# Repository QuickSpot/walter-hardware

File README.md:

# Walter hardware

## Introduction

In this repository you can find all information about Walter's hardware. The
hardware is designed using KiCad but we also support Altium designer footprints.
Besides footprints you can also find:
 - Datasheets
 - 3D renders
 - Schematics

Datasheets are published as PDF and are constructed using LaTeX. We welcome any
pull request on the datasheets to make sure all information that is required is
present.

## License

All files in this repository are published under the GPLv3 license.

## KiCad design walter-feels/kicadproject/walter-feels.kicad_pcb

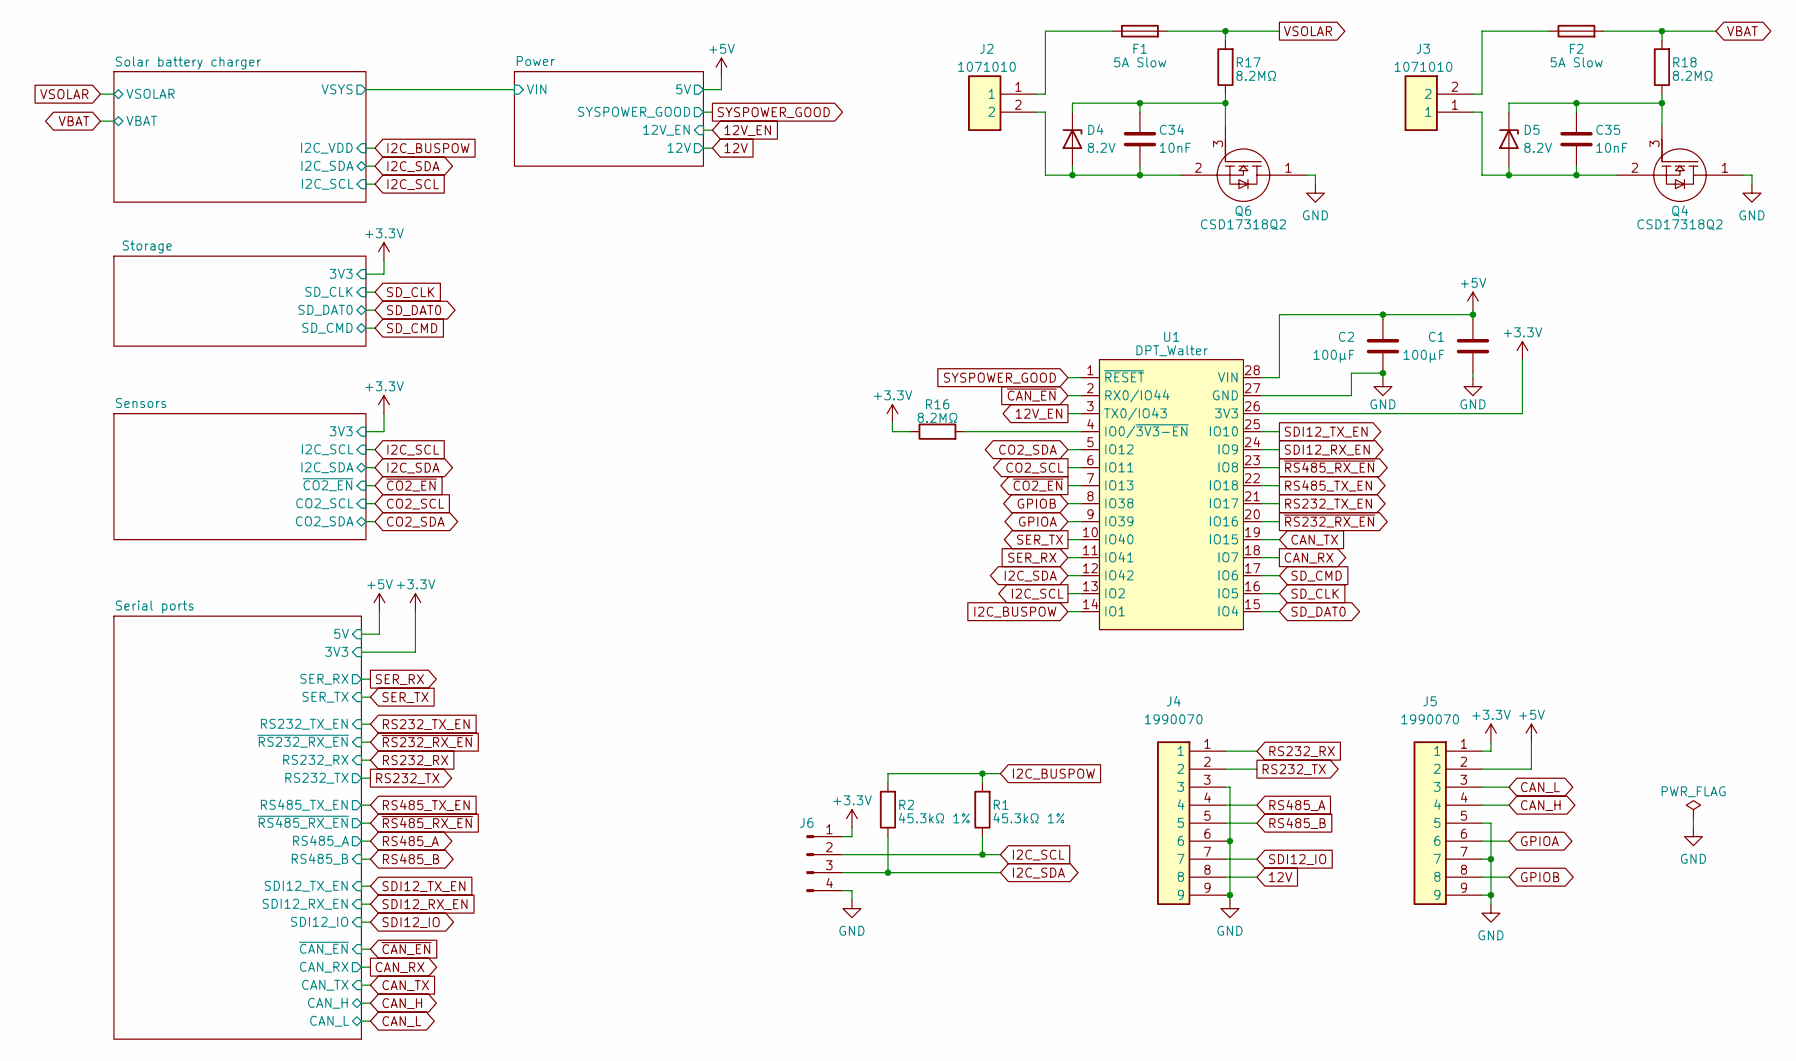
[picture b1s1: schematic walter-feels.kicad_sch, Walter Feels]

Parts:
C1, C2: 100µF; C_1210_3225Metric; JLCPCB C49066
C34, C35: 10nF; C_0603_1608Metric; JLCPCB C57112
D4, D5: 8.2V; D_SOD-523; PARTNO MM5Z8V2T1G; JLCPCB C99679
F1, F2: 5A Slow; Fuse_1206_3216Metric; JLCPCB C2691999
J2, J3: 1071010; JLCPCB C3310307
J4, J5: 1990070; JLCPCB C17275119
J6: Conn_01x04_Male; PinHeader_1x04_P2.54mm_Vertical; JLCPCB C5116483
Q4, Q6: CSD17318Q2
R1, R2: 45.3kΩ 1%; R_0603_1608Metric; JLCPCB C209146
R16, R17, R18: 8.2MΩ; R_0603_1608Metric; JLCPCB C13323
U1: DPT_Walter; walter-socket

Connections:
12V: J4.8; also elsewhere on the board
12V_EN: U1.3 (TX0/IO43); also elsewhere on the board
+3.3V: J5.1, J6.1, R16.1, U1.26 (3V3); also elsewhere on the board
+5V: C1.1, C2.1, J5.2, U1.28 (VIN); also elsewhere on the board
CAN_H: J5.4; also elsewhere on the board
CAN_L: J5.3; also elsewhere on the board
CAN_RX: U1.18 (IO7); also elsewhere on the board
CAN_TX: U1.19 (IO15); also elsewhere on the board
CO2_SCL: U1.6 (IO11); also elsewhere on the board
CO2_SDA: U1.5 (IO12); also elsewhere on the board
GND: C1.2, C2.2, J4.3, J4.6, J4.9, J5.5, J5.7, J5.9, J6.4, Q4.1, Q6.1, U1.27 (GND); also elsewhere on the board
GPIOA: J5.6, U1.9 (IO39)
GPIOB: J5.8, U1.8 (IO38)
I2C_BUSPOW: R1.2, R2.2, U1.14 (IO1); also elsewhere on the board
I2C_SCL: J6.2, R1.1, U1.13 (IO2); also elsewhere on the board
I2C_SDA: J6.3, R2.1, U1.12 (IO42); also elsewhere on the board
unnamed: C34.1, D4.1 (K), Q6.3, R17.1
unnamed: C34.2, D4.2 (A), J2.2, Q6.2
unnamed: C35.1, D5.1 (K), Q4.3, R18.1
unnamed: C35.2, D5.2 (A), J3.1, Q4.2
unnamed: F1.1, J2.1
unnamed: F2.1, J3.2
unnamed: R16.2, U1.4 (IO0/~3V3-EN)
RS232_RX: J4.1; also elsewhere on the board
RS232_TX: J4.2; also elsewhere on the board
RS232_TX_EN: U1.21 (IO17); also elsewhere on the board
RS485_A: J4.4; also elsewhere on the board
RS485_B: J4.5; also elsewhere on the board
RS485_TX_EN: U1.22 (IO18); also elsewhere on the board
SDI12_IO: J4.7; also elsewhere on the board
SDI12_RX_EN: U1.24 (IO9); also elsewhere on the board
SDI12_TX_EN: U1.25 (IO10); also elsewhere on the board
SD_CLK: U1.16 (IO5); also elsewhere on the board
SD_CMD: U1.17 (IO6); also elsewhere on the board
SD_DAT0: U1.15 (IO4); also elsewhere on the board
SER_RX: U1.11 (IO41); also elsewhere on the board
SER_TX: U1.10 (IO40); also elsewhere on the board
SYSPOWER_GOOD: U1.1 (~RESET); also elsewhere on the board
VBAT: F2.2, R18.2; also elsewhere on the board
VSOLAR: F1.2, R17.2; also elsewhere on the board
~CAN_EN: U1.2 (RX0/IO44); also elsewhere on the board
~CO2_EN: U1.7 (IO13); also elsewhere on the board
~RS232_RX_EN: U1.20 (IO16); also elsewhere on the board
~RS485_RX_EN: U1.23 (IO8); also elsewhere on the board

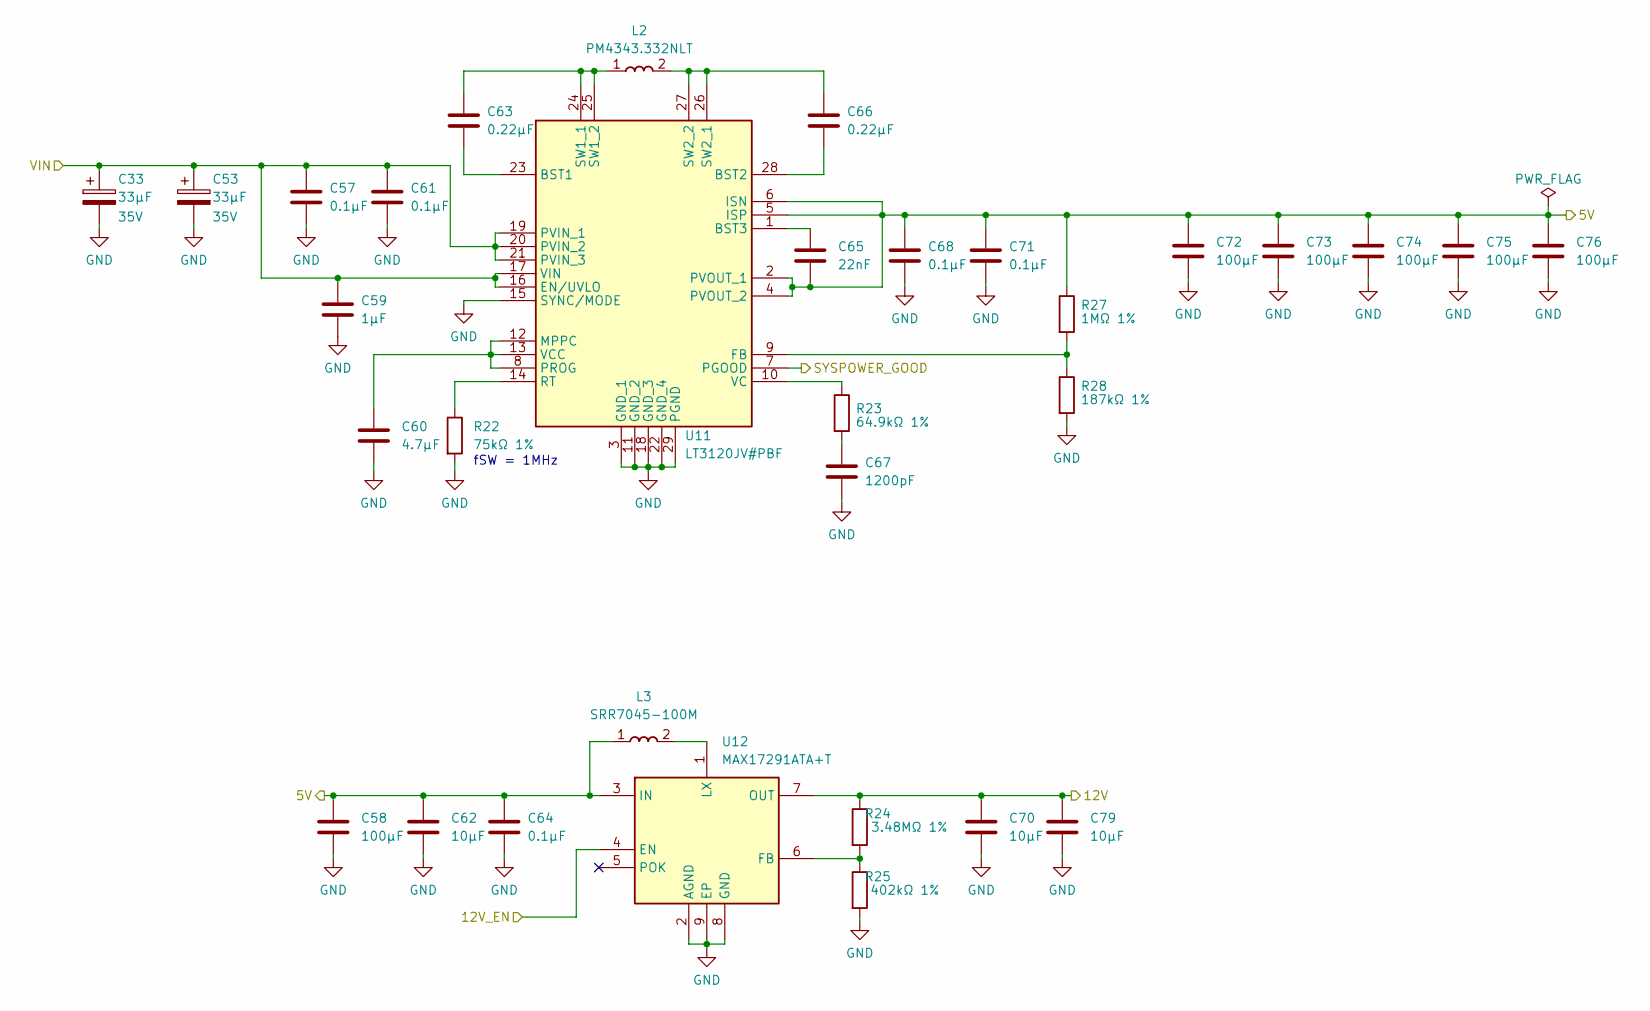
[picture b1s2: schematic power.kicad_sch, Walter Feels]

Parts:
C33, C53: 33µF; CP_EIA-7343-30_AVX-N; Voltage 35V; JLCPCB C2158306
C57, C61, C64, C68, C71: 0.1µF; C_0603_1608Metric; JLCPCB C14663
C58, C72, C73, C74, C75, C76: 100µF; C_1210_3225Metric; JLCPCB C49066
C59: 1μF; C_0603_1608Metric; JLCPCB C15849
C60: 4.7μF; C_0603_1608Metric; JLCPCB C19666
C62, C70, C79: 10µF; C_1206_3216Metric; JLCPCB C13585
C63, C66: 0.22µF; C_0603_1608Metric; JLCPCB C21120
C65: 22nF; C_0603_1608Metric; JLCPCB C21122
C67: 1200pF; C_0603_1608Metric; JLCPCB C30615
L2: PM4343.332NLT; INDPM140128X650N; JLCPCB C2594689
L3: SRR7045-100M; SRR7045100M; JLCPCB C1329516
R22: 75kΩ 1%; R_0603_1608Metric; JLCPCB C23242
R23: 64.9kΩ 1%; R_0603_1608Metric; JLCPCB C14891
R24: 3.48MΩ 1%; R_0603_1608Metric; JLCPCB C422936
R25: 402kΩ 1%; R_0603_1608Metric; JLCPCB C2960796
R27: 1MΩ 1%; R_0603_1608Metric; JLCPCB C22935
R28: 187kΩ 1%; R_0603_1608Metric; JLCPCB C321764
U11: LT3120JV#PBF; QFN50P400X500X83-29N-D; JLCPCB C3198178
U12: MAX17291ATA+T; SON50P200X200X80-9N-D; JLCPCB C7456683

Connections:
12V: C70.1, C79.1, R24.1, U12.7 (OUT); also elsewhere on the board
12V_EN: U12.4 (EN); also elsewhere on the board
+5V: C58.1, C62.1, C64.1, C65.2, C68.1, C71.1, C72.1, C73.1, C74.1, C75.1, C76.1, L3.1, R27.1, U11.2 (PVOUT_1), U11.4 (PVOUT_2), U11.5 (ISP), U11.6 (ISN), U12.3 (IN); also elsewhere on the board
/Power/VIN: C33.1, C53.1, C57.1, C59.2, C61.1, U11.16 (EN/UVLO), U11.17 (VIN), U11.19 (PVIN_1), U11.20 (PVIN_2), U11.21 (PVIN_3); also elsewhere on the board
GND: C33.2, C53.2, C57.2, C58.2, C59.1, C60.1, C61.2, C62.2, C64.2, C67.2, C68.2, C70.2, C71.2, C72.2, C73.2, C74.2, C75.2, C76.2, C79.2, R22.2, R25.2, R28.2, U11.3 (GND_1), U11.11 (GND_2), U11.15 (SYNC/MODE), U11.18 (GND_3), U11.22 (GND_4), U11.29 (PGND), U12.2 (AGND), U12.8 (GND), U12.9 (EP); also elsewhere on the board
unnamed: C60.2, U11.8 (PROG), U11.12 (MPPC), U11.13 (VCC)
unnamed: C63.1, L2.1, U11.24 (SW1_1), U11.25 (SW1_2)
unnamed: C63.2, U11.23 (BST1)
unnamed: C65.1, U11.1 (BST3)
unnamed: C66.1, L2.2, U11.26 (SW2_1), U11.27 (SW2_2)
unnamed: C66.2, U11.28 (BST2)
unnamed: C67.1, R23.2
unnamed: L3.2, U12.1 (LX)
unnamed: R22.1, U11.14 (RT)
unnamed: R23.1, U11.10 (VC)
unnamed: R24.2, R25.1, U12.6 (FB)
unnamed: R27.2, R28.1, U11.9 (FB)
SYSPOWER_GOOD: U11.7 (PGOOD); also elsewhere on the board

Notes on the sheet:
fSW = 1MHz

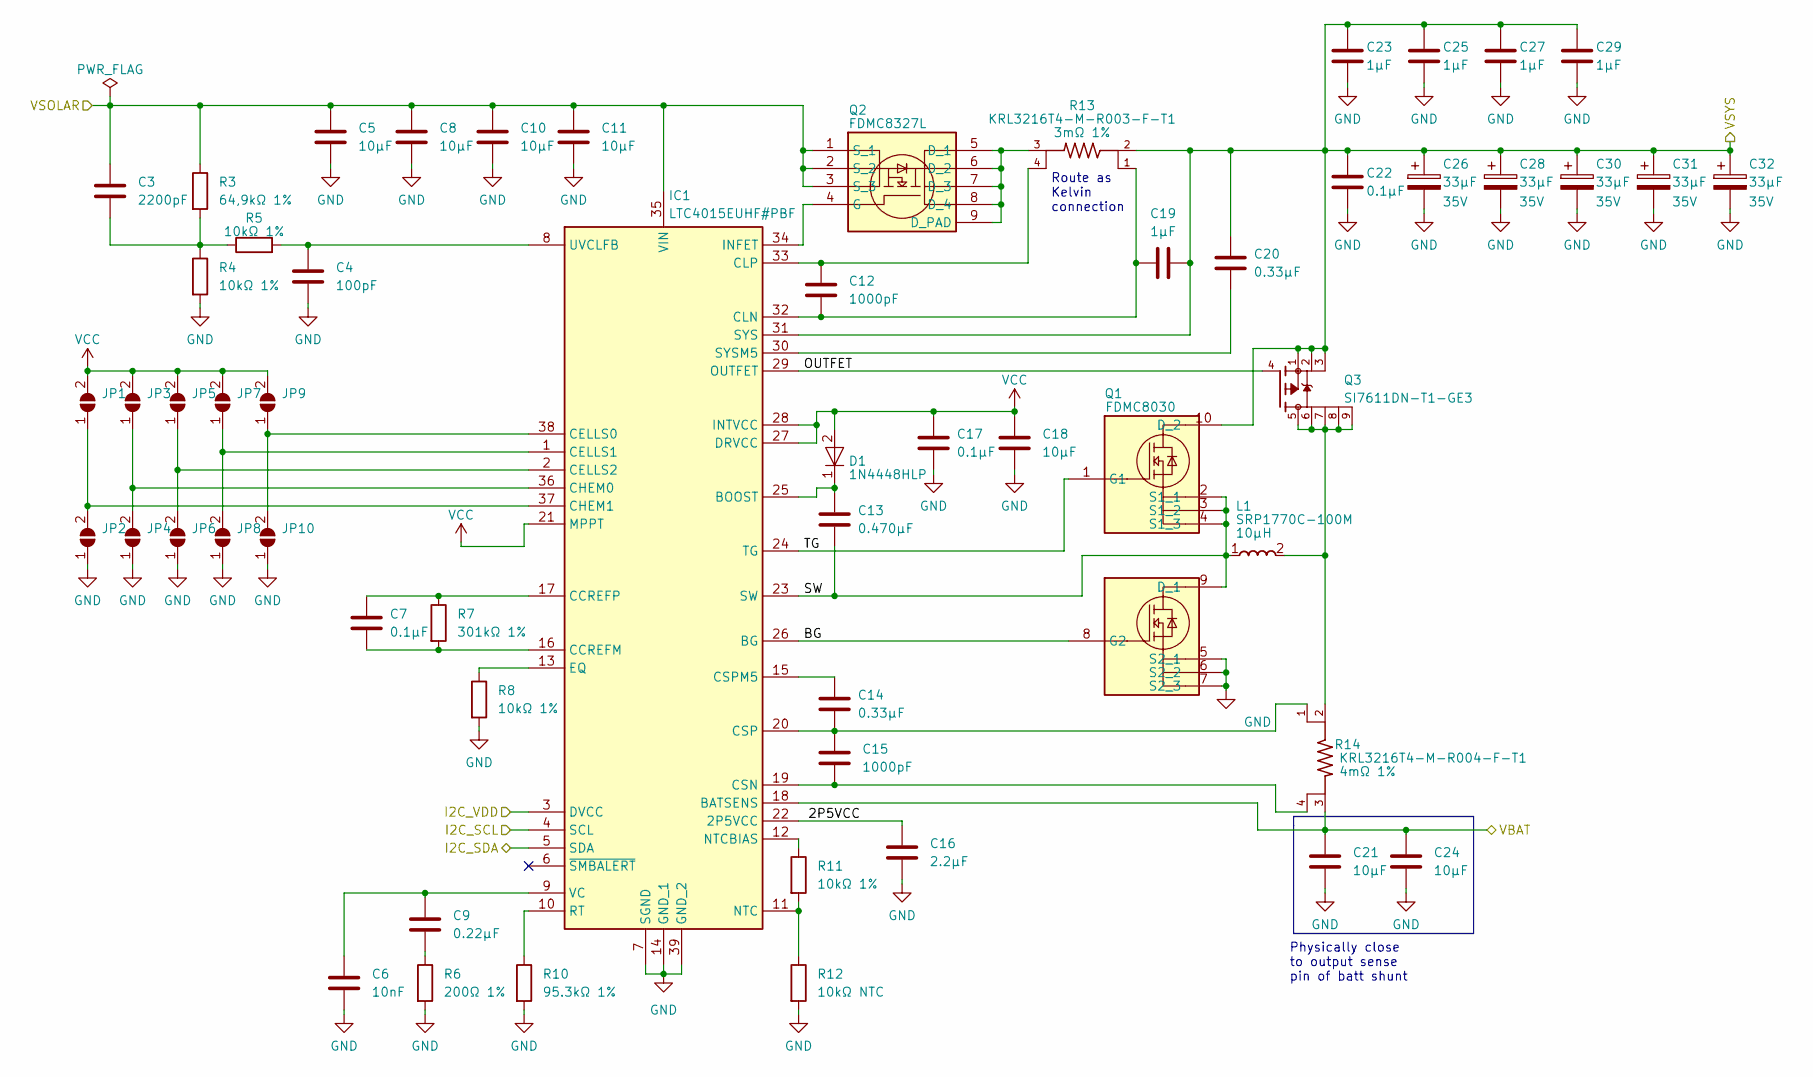
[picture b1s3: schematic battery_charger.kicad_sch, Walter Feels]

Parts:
C3: 2200pF; C_0603_1608Metric; JLCPCB C1604
C4: 100pF; C_0603_1608Metric; JLCPCB C14858
C5, C8, C10, C11, C18, C21, C24: 10µF; C_1206_3216Metric; JLCPCB C13585
C6: 10nF; C_0603_1608Metric; JLCPCB C57112
C7, C17, C22: 0.1µF; C_0603_1608Metric; JLCPCB C14663
C9: 0.22μF; C_0603_1608Metric; JLCPCB C21120
C12, C15: 1000pF; C_0603_1608Metric; JLCPCB C1588
C13: 0.470µF; C_0603_1608Metric; JLCPCB C1623
C14, C20: 0.33μF; C_0603_1608Metric; JLCPCB C1615
C16: 2.2μF; C_0603_1608Metric; JLCPCB C23630
C19, C23, C25, C27, C29: 1μF; C_0603_1608Metric; JLCPCB C15849
C26, C28, C30, C31, C32: 33µF; CP_EIA-7343-30_AVX-N; Voltage 35V; JLCPCB C2158306
D1: 1N4448HLP; DESD3V3S1BL7B; JLCPCB C154874
IC1: LTC4015EUHF#PBF; QFN50P500X700X80-39N-D; Manufacturer_Part_Number LTC4015EUHF#PBF; Mouser Part Number 584-LTC4015EUHF#PBF
JP1, JP2, JP3, JP4, JP5, JP6, JP7, JP8, JP9, JP10: SolderJumper_2_Open; SolderJumper-2_P1.3mm_Open_TrianglePad1.0x1.5mm
L1: SRP1770C-100M; INDPM178169X700N; JLCPCB C1331642
Q1: FDMC8030; FDMC89521L; JLCPCB C890952
Q2: FDMC8327L; FDMC86139P; Mouser Part Number 512-FDMC8327L
Q3: SI7611DN-T1-GE3; VISHAY_SIS468DN-T1-GE3; JLCPCB C506599
R3: 64,9kΩ 1%; R_0603_1608Metric; JLCPCB C137810
R4, R5, R8, R11: 10kΩ 1%; R_0603_1608Metric; JLCPCB C25804
R6: 200Ω 1%; R_0603_1608Metric; JLCPCB C8218
R7: 301kΩ 1%; R_0603_1608Metric; JLCPCB C177982
R10: 95.3kΩ 1%; R_0603_1608Metric; JLCPCB C23267
R12: 10kΩ NTC; R_0603_1608Metric; JLCPCB C13564
R13: KRL3216T4-M-R003-F-T1; RES_KRL3216T4-M-R003-F-T1; JLCPCB C4119998
R14: KRL3216T4-M-R004-F-T1; RES_KRL3216T4-M-R003-F-T1; JLCPCB C2090348

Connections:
/Power/VIN: C19.2, C20.2, C22.1, C23.2, C25.2, C26.1, C27.2, C28.1, C29.2, C30.1, C31.1, C32.1, IC1.31 (SYS), Q1.10 (D_2), Q3.1, Q3.2, Q3.3, R13.2; also elsewhere on the board
/Solar battery charger/2P5VCC: C16.1, IC1.22 (2P5VCC)
/Solar battery charger/BG: IC1.26 (BG), Q1.8 (G2)
/Solar battery charger/OUTFET: IC1.29 (OUTFET), Q3.4
/Solar battery charger/SW: C13.2, IC1.23 (SW), L1.1, Q1.2 (S1_1), Q1.3 (S1_2), Q1.4 (S1_3), Q1.9 (D_1)
/Solar battery charger/TG: IC1.24 (TG), Q1.1 (G1)
GND: C4.2, C5.2, C6.2, C8.2, C10.2, C11.2, C16.2, C17.2, C18.2, C21.2, C22.2, C23.1, C24.2, C25.1, C26.2, C27.1, C28.2, C29.1, C30.2, C31.2, C32.2, IC1.7 (SGND), IC1.14 (GND_1), IC1.39 (GND_2), JP2.1 (A), JP4.1 (A), JP6.1 (A), JP8.1 (A), JP10.1 (A), Q1.5 (S2_1), Q1.6 (S2_2), Q1.7 (S2_3), R4.2, R6.2, R8.2, R10.2, R12.2; also elsewhere on the board
I2C_BUSPOW: IC1.3 (DVCC); also elsewhere on the board
I2C_SCL: IC1.4 (SCL); also elsewhere on the board
I2C_SDA: IC1.5 (SDA); also elsewhere on the board
unnamed: C3.2, R3.2, R4.1, R5.1
unnamed: C4.1, IC1.8 (UVCLFB), R5.2
unnamed: C6.1, C9.1, IC1.9 (VC)
unnamed: C7.1, IC1.17 (CCREFP), R7.1
unnamed: C7.2, IC1.16 (CCREFM), R7.2
unnamed: C9.2, R6.1
unnamed: C12.1, IC1.33 (CLP), R13.4
unnamed: C12.2, C19.1, IC1.32 (CLN), R13.1
unnamed: C13.1, D1.1 (K), IC1.25 (BOOST)
unnamed: C14.1, C15.1, IC1.20 (CSP), R14.1
unnamed: C14.2, IC1.15 (CSPM5)
unnamed: C15.2, IC1.19 (CSN), R14.4
unnamed: C20.1, IC1.30 (SYSM5)
unnamed: IC1.1 (CELLS1), JP7.1 (A), JP8.2 (B)
unnamed: IC1.2 (CELLS2), JP5.1 (A), JP6.2 (B)
unnamed: IC1.10 (RT), R10.1
unnamed: IC1.11 (NTC), R11.2, R12.1
unnamed: IC1.12 (NTCBIAS), R11.1
unnamed: IC1.13 (EQ), R8.1
unnamed: IC1.34 (INFET), Q2.4 (G)
unnamed: IC1.36 (CHEM0), JP3.1 (A), JP4.2 (B)
unnamed: IC1.37 (CHEM1), JP1.1 (A), JP2.2 (B)
unnamed: IC1.38 (CELLS0), JP9.1 (A), JP10.2 (B)
unnamed: L1.2, Q3.5, Q3.6, Q3.7, Q3.8, Q3.9, R14.2
unnamed: Q2.5 (D_1), Q2.6 (D_2), Q2.7 (D_3), Q2.8 (D_4), Q2.9 (D_PAD), R13.3
VBAT: C21.1, C24.1, IC1.18 (BATSENS), R14.3; also elsewhere on the board
VCC: C17.1, C18.1, D1.2 (A), IC1.21 (MPPT), IC1.27 (DRVCC), IC1.28 (INTVCC), JP1.2 (B), JP3.2 (B), JP5.2 (B), JP7.2 (B), JP9.2 (B)
VSOLAR: C3.1, C5.1, C8.1, C10.1, C11.1, IC1.35 (VIN), Q2.1 (S_1), Q2.2 (S_2), Q2.3 (S_3), R3.1; also elsewhere on the board

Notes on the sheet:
Route as Kelvin connection
Physically close to output sense pin of batt shunt

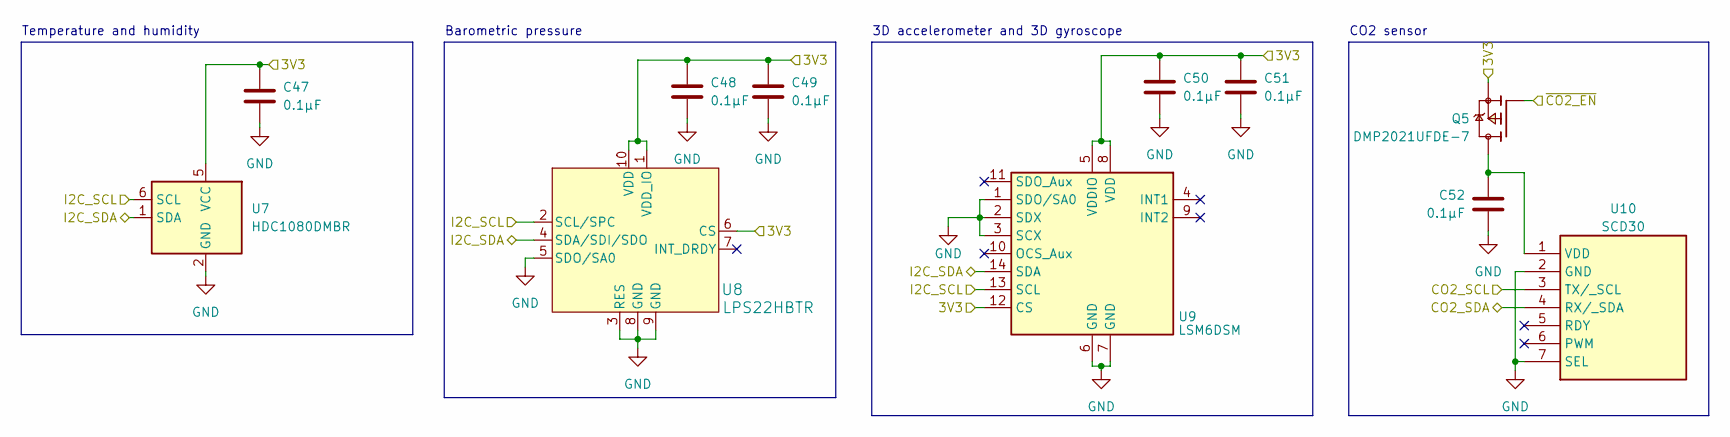
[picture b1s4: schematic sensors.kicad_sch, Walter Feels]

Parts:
C47, C48, C49, C50, C51, C52: 0.1µF; C_0603_1608Metric; JLCPCB C14663
Q5: DMP2021UFDE-7; MOSFET_DMP2066UFDE-7; JLCPCB C151459
U7: HDC1080DMBR; Texas_PWSON-N6; JLCPCB C82227
U8: LPS22HBTR; HLGA10_2X2_STM-L; JLCPCB C94049
U9: LSM6DSM; LGA-14_3x2.5mm_P0.5mm_LayoutBorder3x4y; JLCPCB C94048
U10: SCD30; JLCPCB C1519271

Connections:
+3.3V: C47.1, C48.1, C49.1, C50.1, C51.1, Q5.4, Q5.7, U7.5 (VCC), U8.1 (VDD_IO), U8.6 (CS), U8.10 (VDD), U9.5 (VDDIO), U9.8 (VDD), U9.12 (CS); also elsewhere on the board
CO2_SCL: U10.3 (TX/_SCL); also elsewhere on the board
CO2_SDA: U10.4 (RX/_SDA); also elsewhere on the board
GND: C47.2, C48.2, C49.2, C50.2, C51.2, C52.2, U7.2 (GND), U8.3 (RES), U8.5 (SDO/SA0), U8.8 (GND), U8.9 (GND), U9.1 (SDO/SA0), U9.2 (SDX), U9.3 (SCX), U9.6 (GND), U9.7 (GND), U10.2 (GND), U10.7 (SEL); also elsewhere on the board
I2C_SCL: U7.6 (SCL), U8.2 (SCL/SPC), U9.13 (SCL); also elsewhere on the board
I2C_SDA: U7.1 (SDA), U8.4 (SDA/SDI/SDO), U9.14 (SDA); also elsewhere on the board
unnamed: C52.1, Q5.1, Q5.2, Q5.5, Q5.6, U10.1 (VDD)
~CO2_EN: Q5.3; also elsewhere on the board

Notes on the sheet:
Barometric pressure
Temperature and humidity
3D accelerometer and 3D gyroscope
CO2 sensor

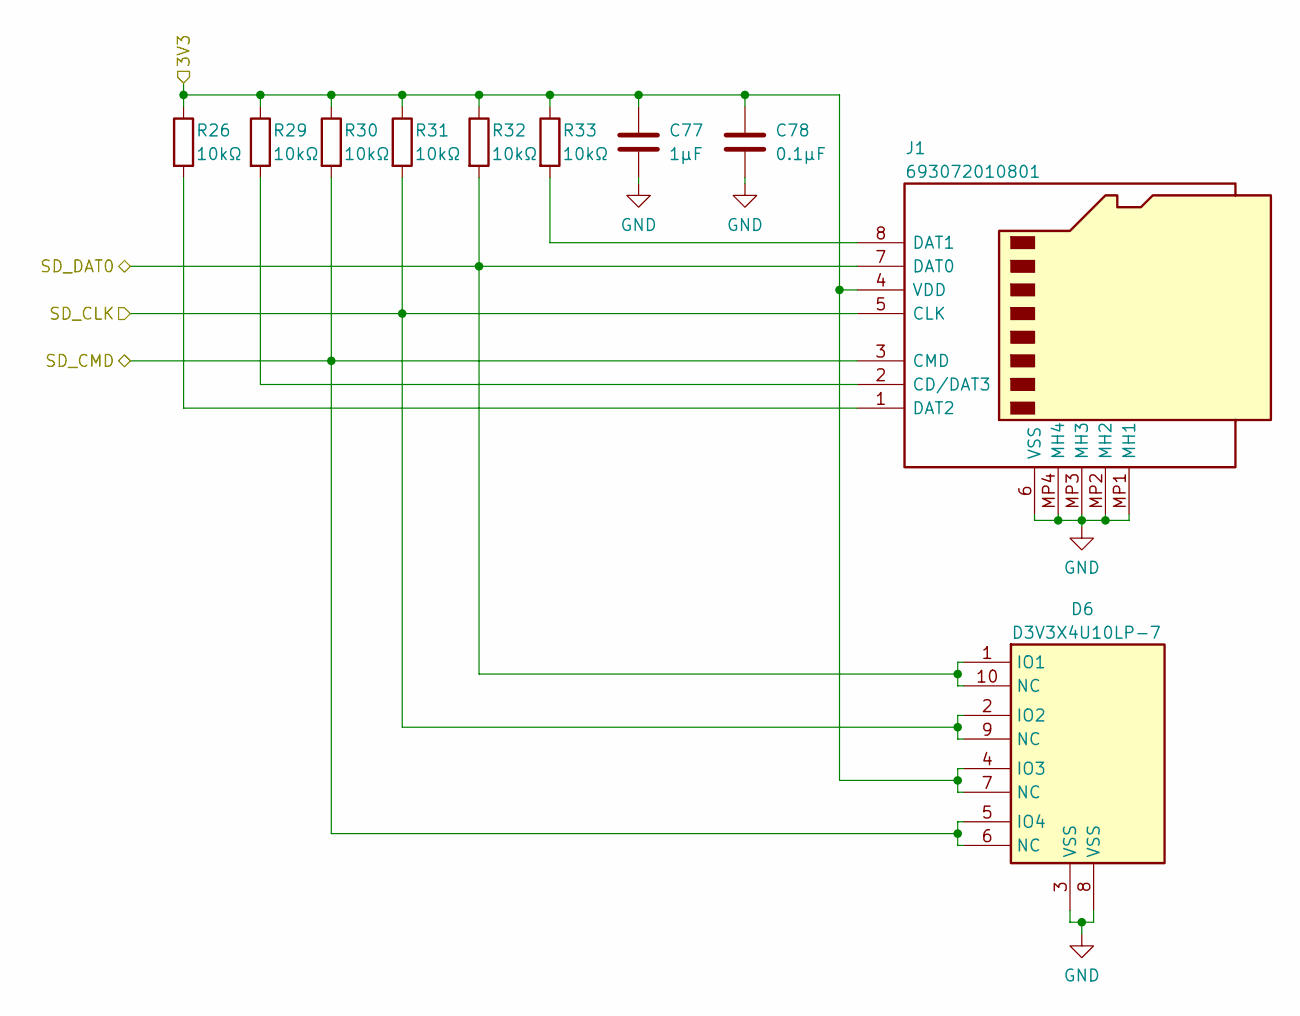
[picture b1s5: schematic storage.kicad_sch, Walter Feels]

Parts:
C77: 1μF; C_0603_1608Metric; JLCPCB C15849
C78: 0.1µF; C_0603_1608Metric; JLCPCB C14663
D6: D3V3X4U10LP-7; D3V3X4U10LP7; JLCPCB C1974550
J1: 693072010801; JLCPCB C5912397
R26, R29, R30, R31, R32, R33: 10kΩ; R_0603_1608Metric; JLCPCB C25804

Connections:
+3.3V: C77.2, C78.1, D6.4 (IO3), D6.7 (NC), J1.4 (VDD), R26.1, R29.1, R30.1, R31.1, R32.1, R33.1; also elsewhere on the board
GND: C77.1, C78.2, D6.3 (VSS), D6.8 (VSS), J1.6 (VSS), J1.MP1 (MH1), J1.MP2 (MH2), J1.MP3 (MH3), J1.MP4 (MH4); also elsewhere on the board
unnamed: J1.1 (DAT2), R26.2
unnamed: J1.2 (CD/DAT3), R29.2
unnamed: J1.8 (DAT1), R33.2
SD_CLK: D6.2 (IO2), D6.9 (NC), J1.5 (CLK), R31.2; also elsewhere on the board
SD_CMD: D6.5 (IO4), D6.6 (NC), J1.3 (CMD), R30.2; also elsewhere on the board
SD_DAT0: D6.1 (IO1), D6.10 (NC), J1.7 (DAT0), R32.2; also elsewhere on the board

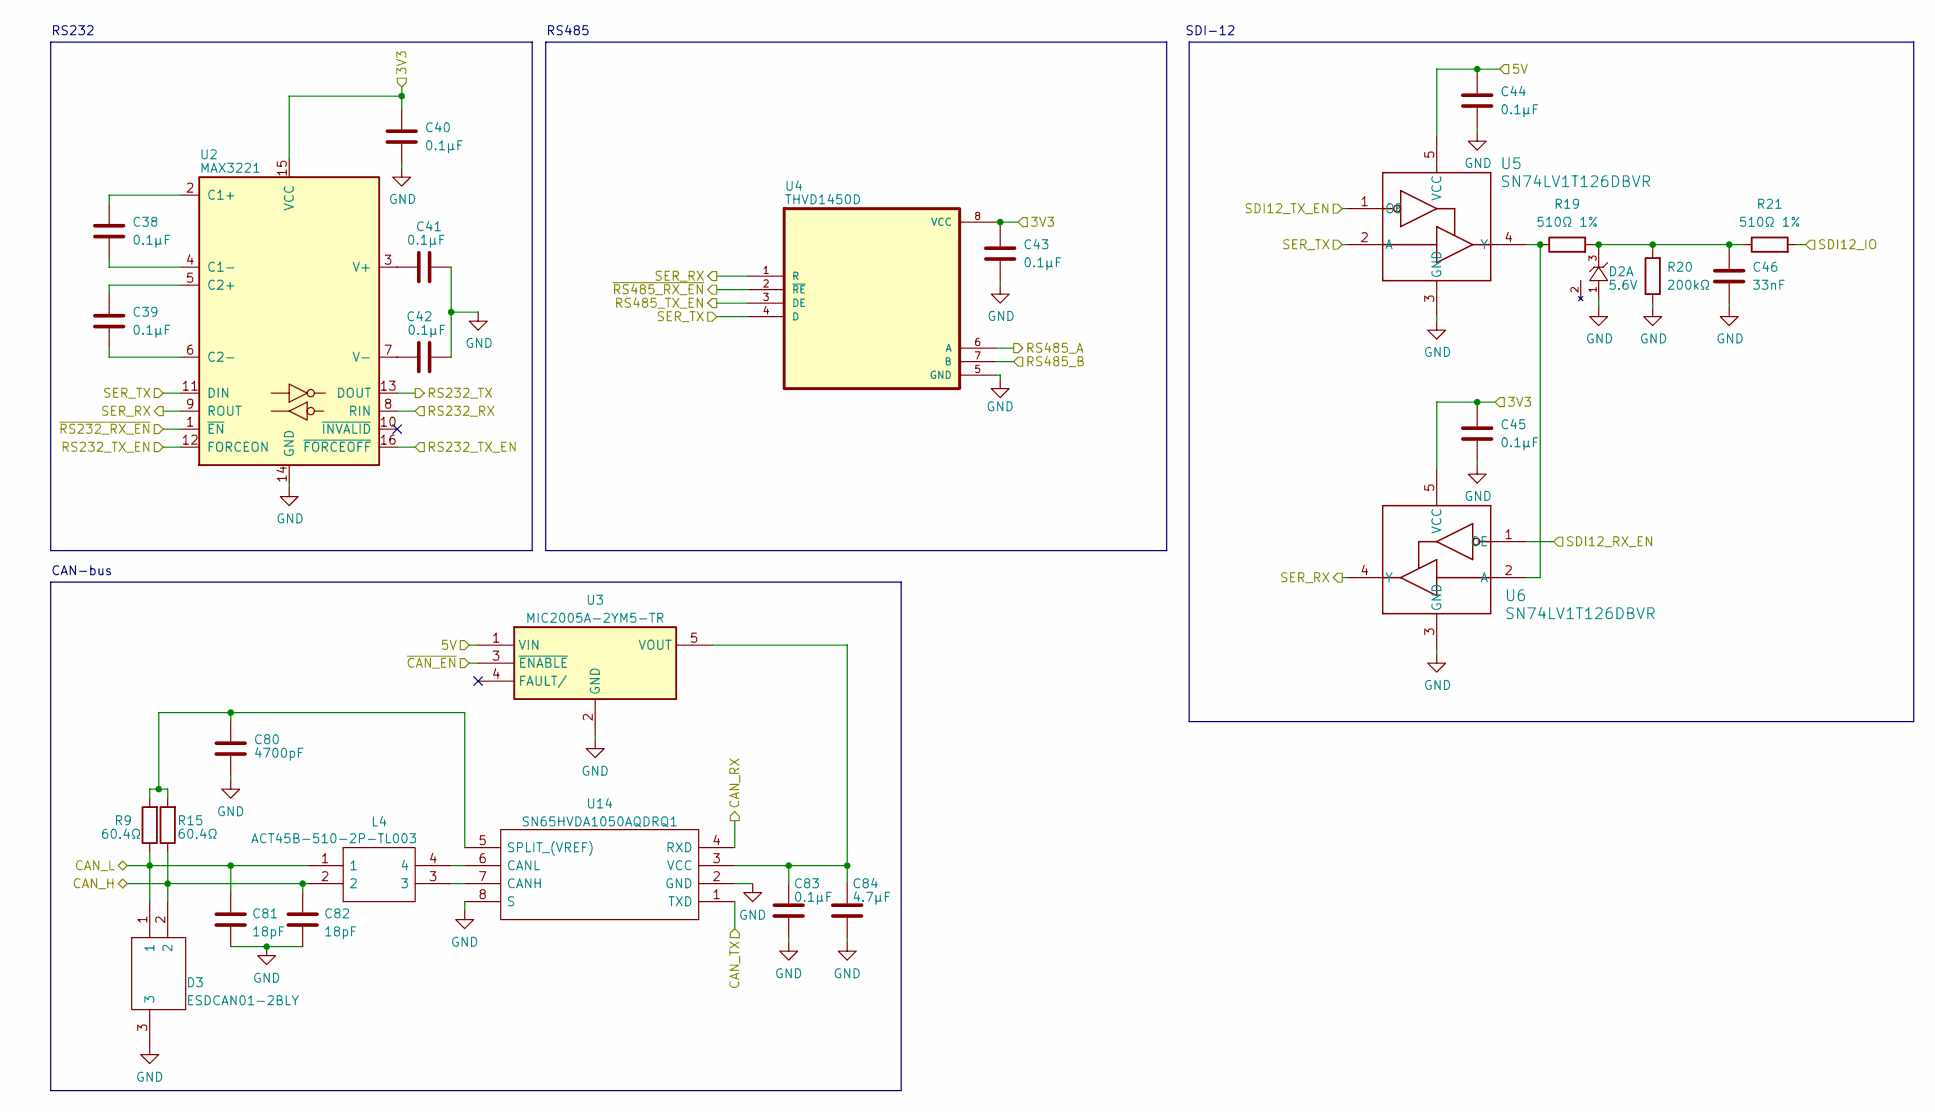
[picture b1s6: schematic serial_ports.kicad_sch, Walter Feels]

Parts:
C38, C39, C40, C41, C42, C43, C44, C45, C83: 0.1µF; C_0603_1608Metric; JLCPCB C14663
C46: 33nF; C_0603_1608Metric; JLCPCB C21117
C80: 4700pF; C_0603_1608Metric; JLCPCB C53987
C81, C82: 18pF; C_0603_1608Metric; JLCPCB C1647
C84: 4.7μF; C_0603_1608Metric; JLCPCB C19666
D2: 5.6V; BZX84C5V6LT1G; PartNo BZX84C5V6LT1G; JLCPCB C82471
D3: ESDCAN01-2BLY; SOT95P255X150-3N; JLCPCB C1976606
L4: ACT45B-510-2P-TL003; ACT45B1012PTL003; JLCPCB C76584
R9, R15: 60.4Ω; R_0603_1608Metric; JLCPCB C2933247
R19, R21: 510Ω 1%; R_0603_1608Metric; JLCPCB C23193
R20: 200kΩ; R_0603_1608Metric; JLCPCB C25811
U2: MAX3221; SOP65P640X110-16N; Partno MAX3221IPWR; JLCPCB C44383
U3: MIC2005A-2YM5-TR; MIC2005A-2YM5; JLCPCB C625654
U4: THVD1450D; SOIC127P599X175-8N; JLCPCB C2671361
U5, U6: SN74LV1T126DBVR; DBV0005A_N; JLCPCB C23654
U14: SN65HVDA1050AQDRQ1; SOIC127P600X175-8N; JLCPCB C115764

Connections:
+3.3V: C40.1, C43.1, C45.1, U2.15 (VCC), U4.8 (VCC), U6.5 (VCC); also elsewhere on the board
+5V: C44.1, U3.1 (VIN), U5.5 (VCC); also elsewhere on the board
CAN_H: C82.1, D3.2, L4.2, R15.1; also elsewhere on the board
CAN_L: C81.1, D3.1, L4.1, R9.1; also elsewhere on the board
CAN_RX: U14.4 (RXD); also elsewhere on the board
CAN_TX: U14.1 (TXD); also elsewhere on the board
GND: C40.2, C41.1, C42.2, C43.2, C44.2, C45.2, C46.2, C80.2, C81.2, C82.2, C83.2, C84.1, D2.1 (A), D3.3, R20.1, U2.14 (GND), U3.2 (GND), U4.5 (GND), U5.3 (GND), U6.3 (GND), U14.2 (GND), U14.8 (S); also elsewhere on the board
unnamed: C38.1, U2.2 (C1+)
unnamed: C38.2, U2.4 (C1-)
unnamed: C39.1, U2.5 (C2+)
unnamed: C39.2, U2.6 (C2-)
unnamed: C41.2, U2.3 (V+)
unnamed: C42.1, U2.7 (V-)
unnamed: C46.1, D2.3 (K), R19.2, R20.2, R21.1
unnamed: C80.1, R9.2, R15.2, U14.5 (SPLIT_(VREF))
unnamed: C83.1, C84.2, U3.5 (VOUT), U14.3 (VCC)
unnamed: L4.3, U14.7 (CANH)
unnamed: L4.4, U14.6 (CANL)
unnamed: R19.1, U5.4 (Y), U6.2 (A)
RS232_RX: U2.8 (RIN); also elsewhere on the board
RS232_TX: U2.13 (DOUT); also elsewhere on the board
RS232_TX_EN: U2.12 (FORCEON), U2.16 (~FORCEOFF); also elsewhere on the board
RS485_A: U4.6 (A); also elsewhere on the board
RS485_B: U4.7 (B); also elsewhere on the board
RS485_TX_EN: U4.3 (DE); also elsewhere on the board
SDI12_IO: R21.2; also elsewhere on the board
SDI12_RX_EN: U6.1 (OE); also elsewhere on the board
SDI12_TX_EN: U5.1 (OE); also elsewhere on the board
SER_RX: U2.9 (ROUT), U4.1 (R), U6.4 (Y); also elsewhere on the board
SER_TX: U2.11 (DIN), U4.4 (D), U5.2 (A); also elsewhere on the board
~CAN_EN: U3.3 (~ENABLE); also elsewhere on the board
~RS232_RX_EN: U2.1 (~EN); also elsewhere on the board
~RS485_RX_EN: U4.2 (~RE); also elsewhere on the board

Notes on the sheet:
CAN-bus
RS232
SDI-12
RS485

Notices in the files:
walter-feels/kicadproject/battery_charger.kicad_sch:
License: GPLv3
